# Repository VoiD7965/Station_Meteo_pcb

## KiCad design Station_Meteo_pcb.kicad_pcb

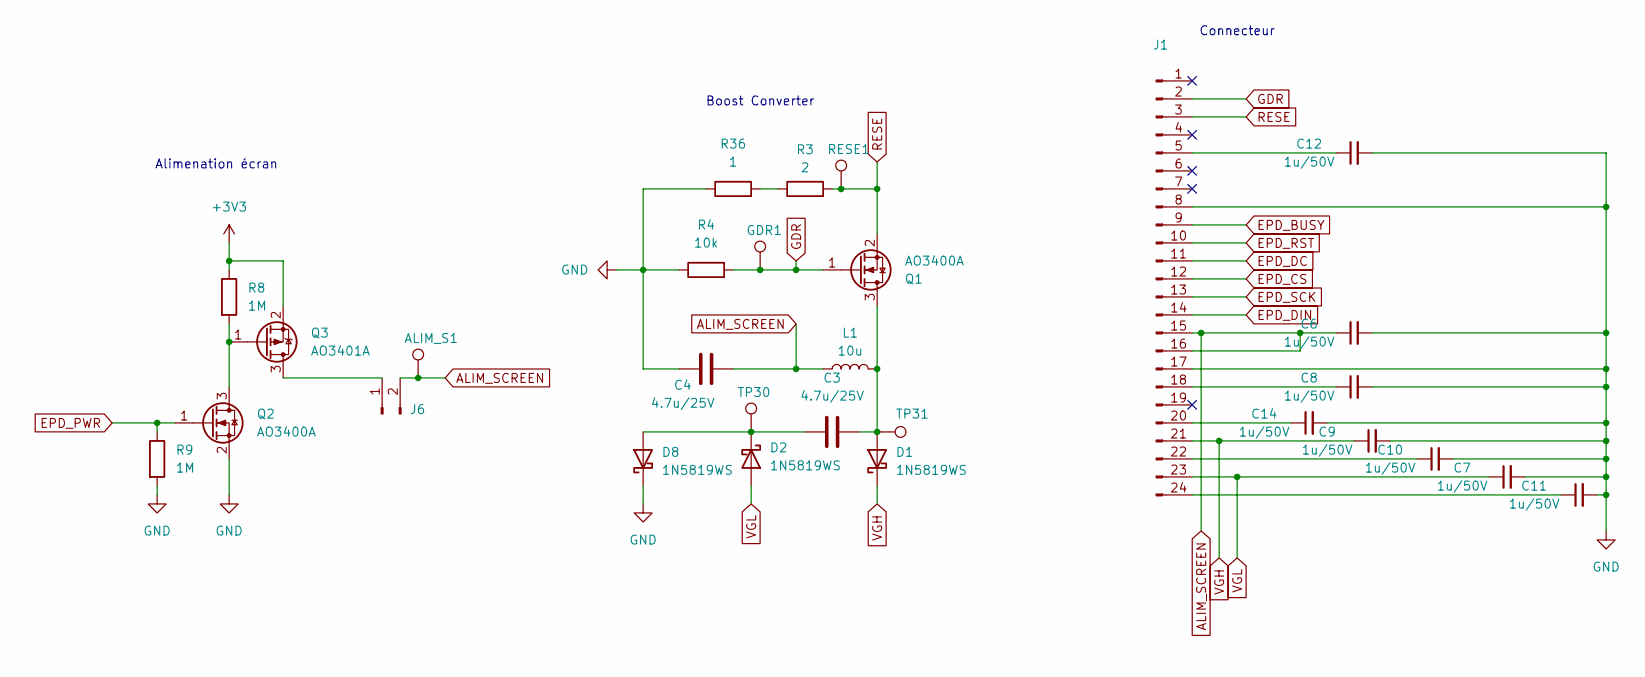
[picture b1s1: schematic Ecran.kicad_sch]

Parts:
ALIM_S1: TestPoint; TestPoint_Pad_D1.5mm
C3, C4: 4.7u/25V; C_0805_2012Metric; LCSC C1779
C6, C7, C8, C9, C10, C11, C12, C14: 1u/50V; C_0603_1608Metric; LCSC C15849
D1, D2, D8: 1N5819WS; D_SOD-323; LCSC C191023
GDR1: TestPoint; TestPoint_Pad_D1.5mm
J1: ZX-FPC-FWSX0.5PH224; Connector_1x24_epaper; LCSC C7419878
J6: DZ254S-11-02-48; PinHeader_1x02_P2.54mm_Vertical_SMD_Pin1Left; LCSC C5160785
L1: 10u; L_0805_2012Metric; LCSC C1046
Q1, Q2: AO3400A; SOT-23; LCSC C20917
Q3: AO3401A; SOT-23; LCSC C15127
R3: 2; R_0603_1608Metric; LCSC C22977
R4: 10k; R_0603_1608Metric; LCSC C25804
R8, R9: 1M; R_0603_1608Metric; LCSC C22935
R36: 1; R_0603_1608Metric; LCSC C22936
RESE1: TestPoint; TestPoint_Pad_D1.5mm
TP30, TP31: TestPoint; TestPoint_Pad_D1.5mm

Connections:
+3V3: Q3.2 (S), R8.1; also elsewhere on the board
ALIM_SCREEN: ALIM_S1.1, C4.2, C6.1, J1.15, J1.16, J6.2, L1.1
EPD_BUSY: J1.9; also elsewhere on the board
EPD_CS: J1.12; also elsewhere on the board
EPD_DC: J1.11; also elsewhere on the board
EPD_DIN: J1.14; also elsewhere on the board
EPD_PWR: Q2.1 (G), R9.1; also elsewhere on the board
EPD_RST: J1.10; also elsewhere on the board
EPD_SCK: J1.13; also elsewhere on the board
GDR: GDR1.1, J1.2, Q1.1 (G), R4.2
GND: C4.1, C6.2, C7.2, C8.2, C9.2, C10.2, C11.2, C12.2, C14.2, D8.1 (K), J1.8, J1.17, Q2.2 (S), R4.1, R9.2, R36.1; also elsewhere on the board
unnamed: C3.2, D1.2 (A), L1.2, Q1.3 (D), TP31.1
unnamed: C3.1, D2.1 (K), D8.2 (A), TP30.1
unnamed: C12.1, J1.5
unnamed: C8.1, J1.18
unnamed: C14.1, J1.20
unnamed: C10.1, J1.22
unnamed: C11.1, J1.24
unnamed: J6.1, Q3.3 (D)
unnamed: Q2.3 (D), Q3.1 (G), R8.2
unnamed: R3.1, R36.2
RESE: J1.3, Q1.2 (S), R3.2, RESE1.1
VGH: C9.1, D1.1 (K), J1.21
VGL: C7.1, D2.2 (A), J1.23

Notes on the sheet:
Alimenation écran
Boost Converter
Connecteur

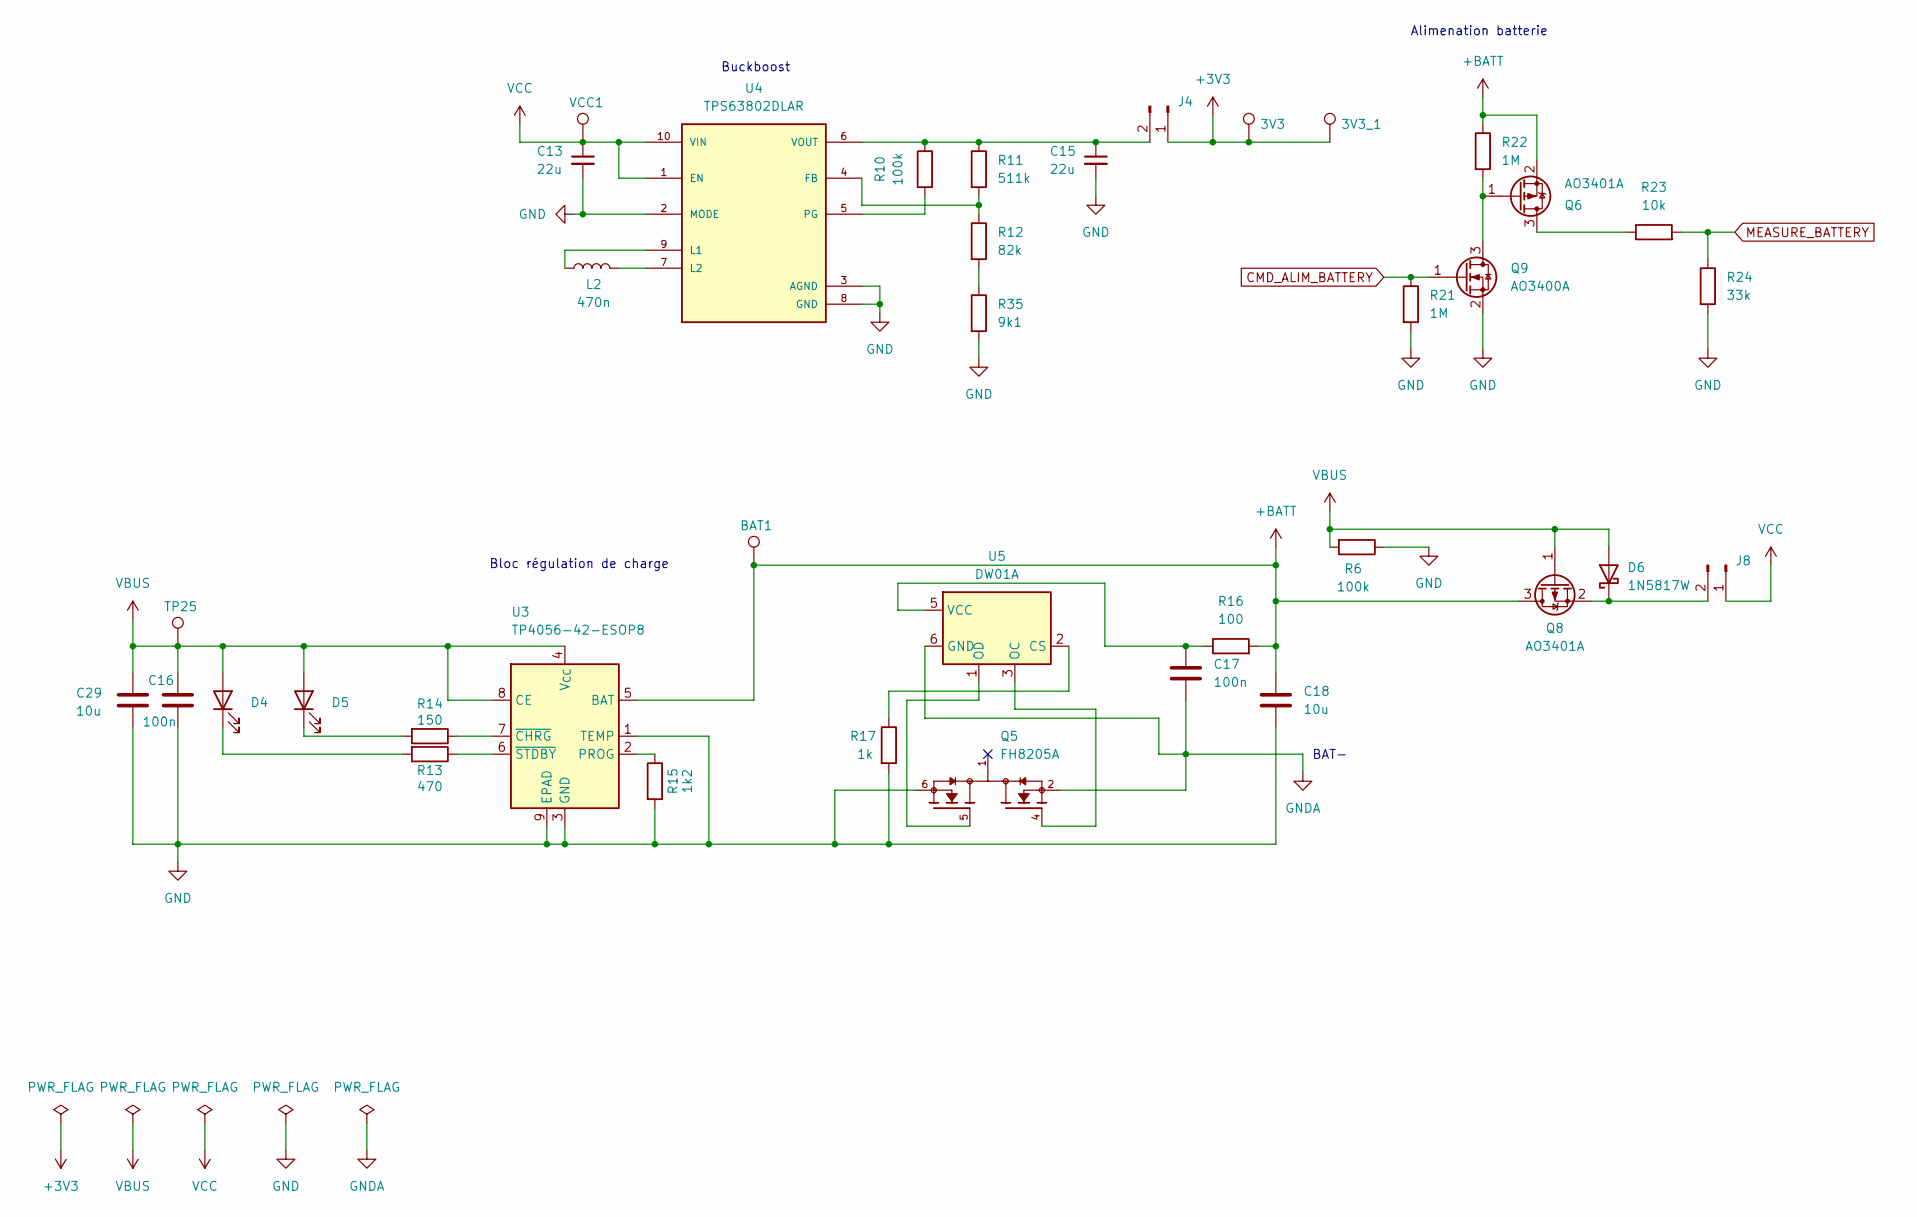
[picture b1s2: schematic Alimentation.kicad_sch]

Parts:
3V3, 3V3_1: TestPoint; TestPoint_Pad_D1.5mm
BAT1: TestPoint; TestPoint_Pad_D1.5mm
C13, C15: 22u; C_0603_1608Metric; LCSC C59461
C16, C17: 100n; C_0402_1005Metric; LCSC C1525
C18, C29: 10u; C_0603_1608Metric; LCSC C19702
D4: KT-0603W; LED_0603_1608Metric; LCSC C2290
D5: KT-0603R; LED_0603_1608Metric; LCSC C2286
D6: 1N5817W; D_SOD-123; LCSC C5185908
J4, J8: DZ254S-11-02-48; PinHeader_1x02_P2.54mm_Vertical_SMD_Pin1Left; LCSC C5160785
L2: 470n; SPM4030T-R47M-HZ; LCSC C531455
Q5: FH8205A; FS8205A; PARTREV 1.7; LCSC C2929075
Q6, Q8: AO3401A; SOT-23; LCSC C15127
Q9: AO3400A; SOT-23; LCSC C20917
R6, R10: 100k; R_0603_1608Metric; LCSC C25803
R11: 511k; R_0603_1608Metric; LCSC C23192
R12: 82k; R_0603_1608Metric; LCSC C23254
R13: 470; R_0603_1608Metric; LCSC C23179
R14: 150; R_0603_1608Metric; LCSC C22808
R15: 1k2; R_0603_1608Metric; LCSC C22765
R16: 100; R_0603_1608Metric; LCSC C22775
R17: 1k; R_0603_1608Metric; LCSC C21190
R21, R22: 1M; R_0603_1608Metric; LCSC C22935
R23: 10k; R_0603_1608Metric; LCSC C25804
R24: 33k; R_0603_1608Metric; LCSC C4216
R35: 9k1; R_0603_1608Metric; LCSC C23260
TP25: TestPoint; TestPoint_Pad_D1.5mm
U3: TP4056-42-ESOP8; SOIC-8-1EP_3.9x4.9mm_P1.27mm_EP2.41x3.3mm_ThermalVias; LCSC C16581
U4: TPS63802DLAR; VREG_TPS63802DLAR; PARTREV B; LCSC C2845237
U5: DW01A; SOT-23-6; LCSC C42380662
VCC1: TestPoint; TestPoint_Pad_D1.5mm

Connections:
+3V3: 3V3.1, 3V3_1.1, J4.1; also elsewhere on the board
+BATT: BAT1.1, C18.1, Q6.2 (S), Q8.3 (D), R16.2, R22.1, U3.5 (BAT); also elsewhere on the board
CMD_ALIM_BATTERY: Q9.1 (G), R21.1; also elsewhere on the board
GND: C13.2, C15.2, C16.2, C18.2, C29.1, Q5.6, Q5.7, Q9.2 (S), R6.1, R15.2, R17.2, R21.2, R24.2, R35.2, U3.1 (TEMP), U3.3 (GND), U3.9 (EPAD), U4.2 (MODE), U4.3 (AGND), U4.8 (GND); also elsewhere on the board
GNDA: C17.2, Q5.2, Q5.3, U5.6 (GND); also elsewhere on the board
MEASURE_BATTERY: R23.2, R24.1; also elsewhere on the board
unnamed: D4.1 (K), R13.2
unnamed: D5.1 (K), R14.2
unnamed: D6.1 (K), J8.2, Q8.2 (S)
unnamed: C15.1, J4.2, R10.1, R11.1, U4.6 (VOUT)
unnamed: Q6.3 (D), R23.1
unnamed: Q6.1 (G), Q9.3 (D), R22.2
unnamed: R12.2, R35.1
unnamed: R15.1, U3.2 (PROG)
unnamed: R14.1, U3.7 (~CHRG)
unnamed: R13.1, U3.6 (~STDBY)
unnamed: R11.2, R12.1, U4.4 (FB)
unnamed: L2.1, U4.9 (L1)
unnamed: L2.2, U4.7 (L2)
unnamed: R10.2, U4.5 (PG)
unnamed: R17.1, U5.2 (CS)
unnamed: Q5.4, U5.3 (OC)
unnamed: Q5.5, U5.1 (OD)
unnamed: C17.1, R16.1, U5.5 (VCC)
VBUS: C16.1, C29.2, D4.2 (A), D5.2 (A), D6.2 (A), Q8.1 (G), R6.2, TP25.1, U3.4 (V_{CC}), U3.8 (CE); also elsewhere on the board
VCC: C13.1, J8.1, U4.1 (EN), U4.10 (VIN), VCC1.1

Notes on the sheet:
BAT-
Alimenation batterie
Buckboost
Bloc régulation de charge

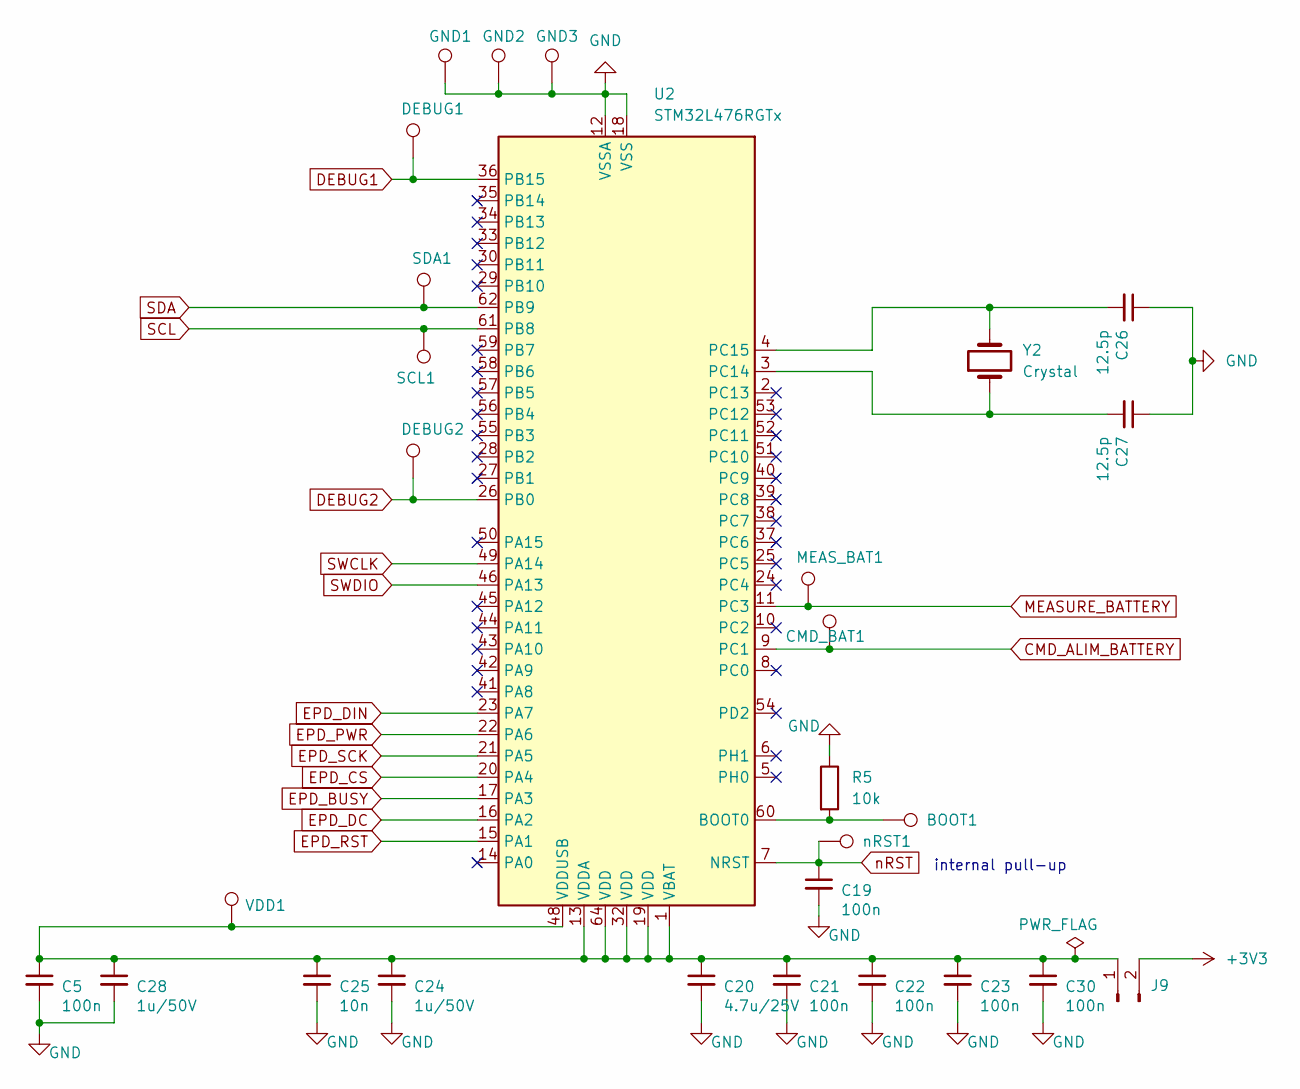
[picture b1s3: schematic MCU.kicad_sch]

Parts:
BOOT1: TestPoint; TestPoint_Pad_D1.5mm
C5, C19, C21, C22, C23, C30: 100n; C_0402_1005Metric; LCSC C1525
C20: 4.7u/25V; C_0805_2012Metric; LCSC C1779
C24, C28: 1u/50V; C_0603_1608Metric; LCSC C15849
C25: 10n; C_0603_1608Metric; LCSC C57112
C26, C27: 12.5p; C_0402_1005Metric; LCSC C1547
CMD_BAT1: TestPoint; TestPoint_Pad_D1.5mm
DEBUG1, DEBUG2: TestPoint; TestPoint_Pad_D1.5mm
GND1, GND2, GND3: TestPoint; TestPoint_Pad_D1.5mm
J9: DZ254S-11-02-48; PinHeader_1x02_P2.54mm_Vertical_SMD_Pin1Left; LCSC C5160785
MEAS_BAT1: TestPoint; TestPoint_Pad_D1.5mm
R5: 10k; R_0603_1608Metric; LCSC C25804
SCL1: TestPoint; TestPoint_Pad_D1.5mm
SDA1: TestPoint; TestPoint_Pad_D1.5mm
U2: STM32L476RGTx; LQFP-64_10x10mm_P0.5mm; LCSC C74797
VDD1: TestPoint; TestPoint_Pad_D1.5mm
Y2: Crystal; Crystal_SMD_3215-2Pin_3.2x1.5mm; LCSC C2450907
nRST1: TestPoint; TestPoint_Pad_D1.5mm

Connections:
+3V3: J9.2; also elsewhere on the board
CMD_ALIM_BATTERY: CMD_BAT1.1, U2.9 (PC1); also elsewhere on the board
DEBUG1: DEBUG1.1, U2.36 (PB15)
DEBUG2: DEBUG2.1, U2.26 (PB0)
EPD_BUSY: U2.17 (PA3); also elsewhere on the board
EPD_CS: U2.20 (PA4); also elsewhere on the board
EPD_DC: U2.16 (PA2); also elsewhere on the board
EPD_DIN: U2.23 (PA7); also elsewhere on the board
EPD_PWR: U2.22 (PA6); also elsewhere on the board
EPD_RST: U2.15 (PA1); also elsewhere on the board
EPD_SCK: U2.21 (PA5); also elsewhere on the board
GND: C5.2, C19.2, C20.2, C21.2, C22.2, C23.2, C24.2, C25.2, C26.1, C27.1, C28.2, C30.2, GND1.1, GND2.1, GND3.1, R5.1, U2.12 (VSSA), U2.18 (VSS), U2.31 (VSS), U2.47 (VSS), U2.63 (VSS); also elsewhere on the board
MEASURE_BATTERY: MEAS_BAT1.1, U2.11 (PC3); also elsewhere on the board
unnamed: C5.1, C20.1, C21.1, C22.1, C23.1, C24.1, C25.1, C28.1, C30.1, J9.1, U2.1 (VBAT), U2.13 (VDDA), U2.19 (VDD), U2.32 (VDD), U2.48 (VDDUSB), U2.64 (VDD), VDD1.1
unnamed: BOOT1.1, R5.2, U2.60 (BOOT0)
unnamed: C27.2, U2.3 (PC14), Y2.1
unnamed: C26.2, U2.4 (PC15), Y2.2
SCL: SCL1.1, U2.61 (PB8); also elsewhere on the board
SDA: SDA1.1, U2.62 (PB9); also elsewhere on the board
SWCLK: U2.49 (PA14); also elsewhere on the board
SWDIO: U2.46 (PA13); also elsewhere on the board
nRST: C19.1, U2.7 (NRST), nRST1.1; also elsewhere on the board

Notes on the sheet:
internal pull-up

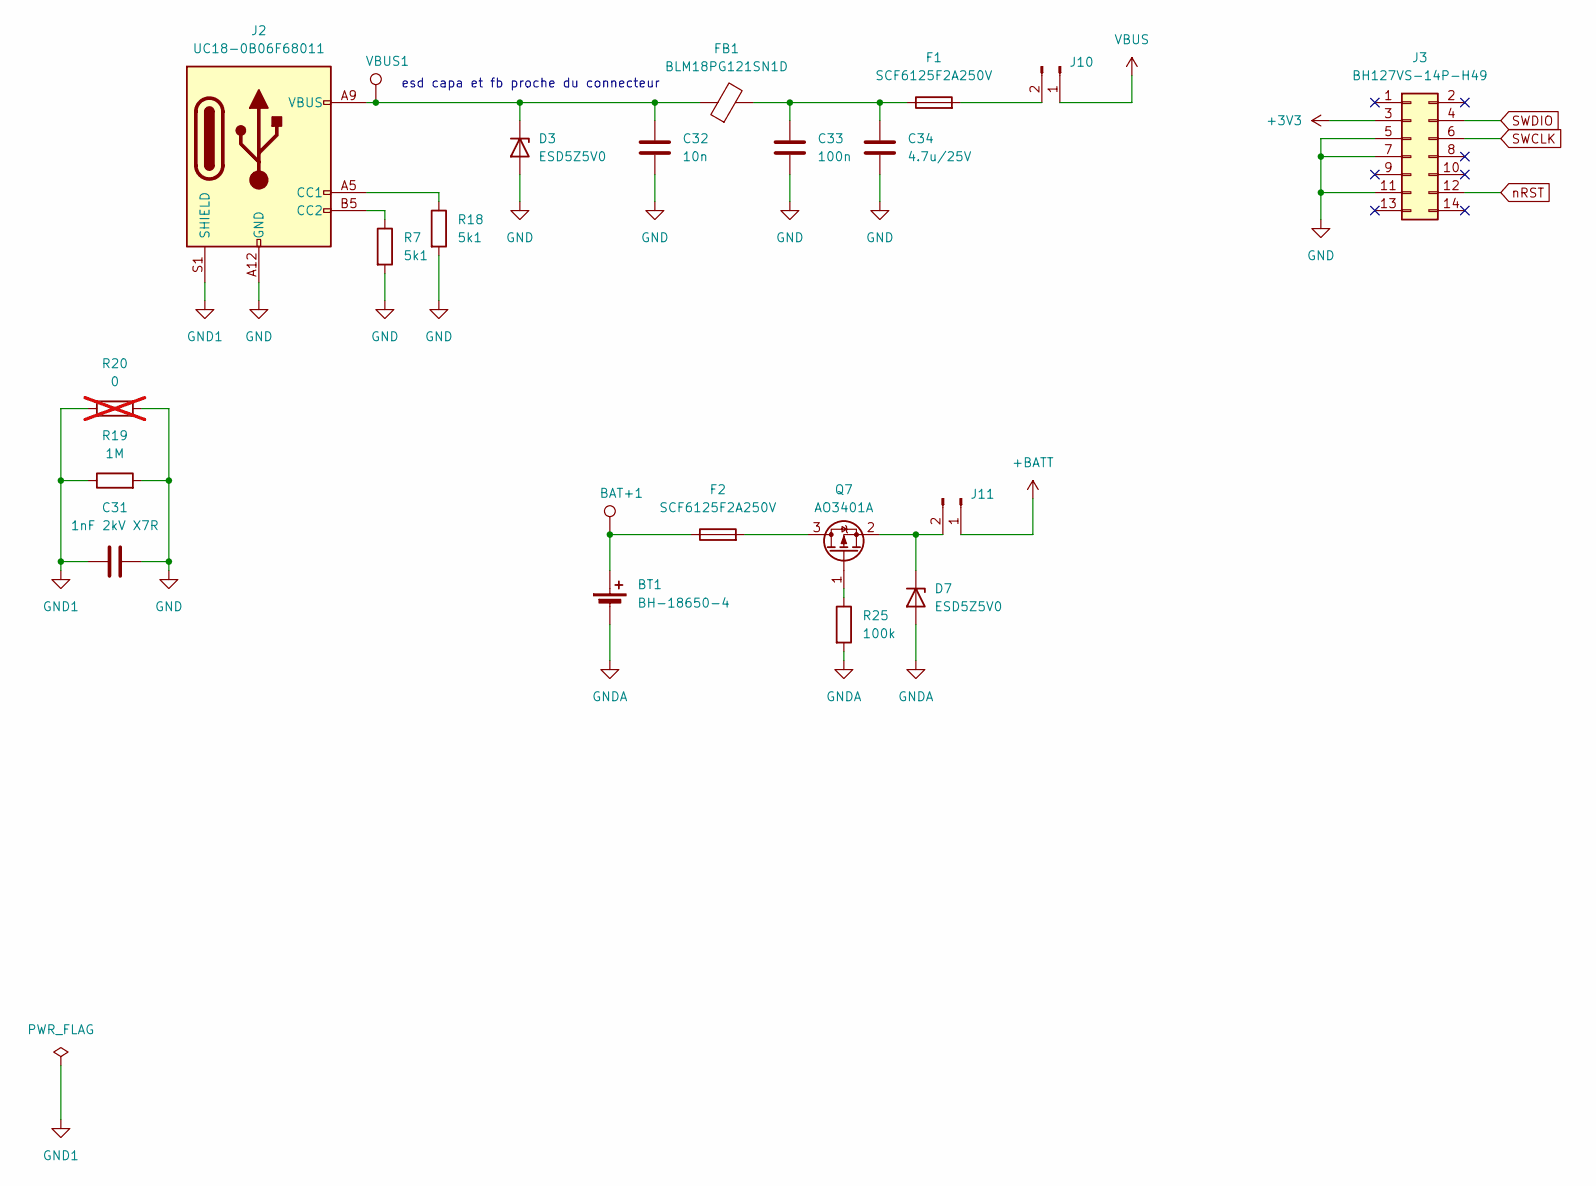
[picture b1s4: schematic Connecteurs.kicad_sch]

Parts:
BAT+1: TestPoint; TestPoint_Pad_D1.5mm
BT1: BH-18650-4; LCSC C7525438
C31: 1nF 2kV X7R; C_1206_3216Metric; LCSC C9196
C32: 10n; C_0603_1608Metric; LCSC C57112
C33: 100n; C_0402_1005Metric; LCSC C1525
C34: 4.7u/25V; C_0805_2012Metric; LCSC C1779
D3, D7: ESD5Z5V0; D_SOD-523; LCSC C21714169
F1, F2: SCF6125F2A250V; LCSC C19712554
FB1: BLM18PG121SN1D; L_0603_1608Metric; LCSC C14709
J2: UC18-0B06F68011; LCSC C36936555
J3: BH127VS-14P-H49; Connector_STLINKV3_Minie_14P; LCSC C42462827
J10, J11: DZ254S-11-02-48; PinHeader_1x02_P2.54mm_Vertical_SMD_Pin1Left; LCSC C5160785
Q7: AO3401A; SOT-23; LCSC C15127
R7, R18: 5k1; R_0603_1608Metric; LCSC C23186
R19: 1M; R_0603_1608Metric; LCSC C22935
R20: 0; R_0603_1608Metric; not fitted
R25: 100k; R_0603_1608Metric; LCSC C25803
VBUS1: TestPoint; TestPoint_Pad_D1.5mm

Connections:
+3V3: J3.3; also elsewhere on the board
+BATT: J11.1; also elsewhere on the board
GND: C31.2, C32.2, C33.2, C34.2, D3.2 (A), J2.A12 (GND), J2.B12 (GND), J3.5, J3.7, J3.11, R7.2, R18.2, R19.2, R20.2; also elsewhere on the board
GND1: C31.1, J2.S1 (SHIELD), R19.1, R20.1
GNDA: BT1.2 (-), D7.2 (A), R25.2; also elsewhere on the board
unnamed: BAT+1.1, BT1.1 (+), F2.1
unnamed: C33.1, C34.1, F1.1, FB1.2
unnamed: C32.1, D3.1 (K), FB1.1, J2.A9 (VBUS), J2.B9 (VBUS), VBUS1.1
unnamed: D7.1 (K), J11.2, Q7.2 (S)
unnamed: J2.A5 (CC1), R18.1
unnamed: J2.B5 (CC2), R7.1
unnamed: F1.2, J10.2
unnamed: F2.2, Q7.3 (D)
unnamed: Q7.1 (G), R25.1
SWCLK: J3.6; also elsewhere on the board
SWDIO: J3.4; also elsewhere on the board
VBUS: J10.1; also elsewhere on the board
nRST: J3.12; also elsewhere on the board

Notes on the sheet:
esd capa et fb proche du connecteur

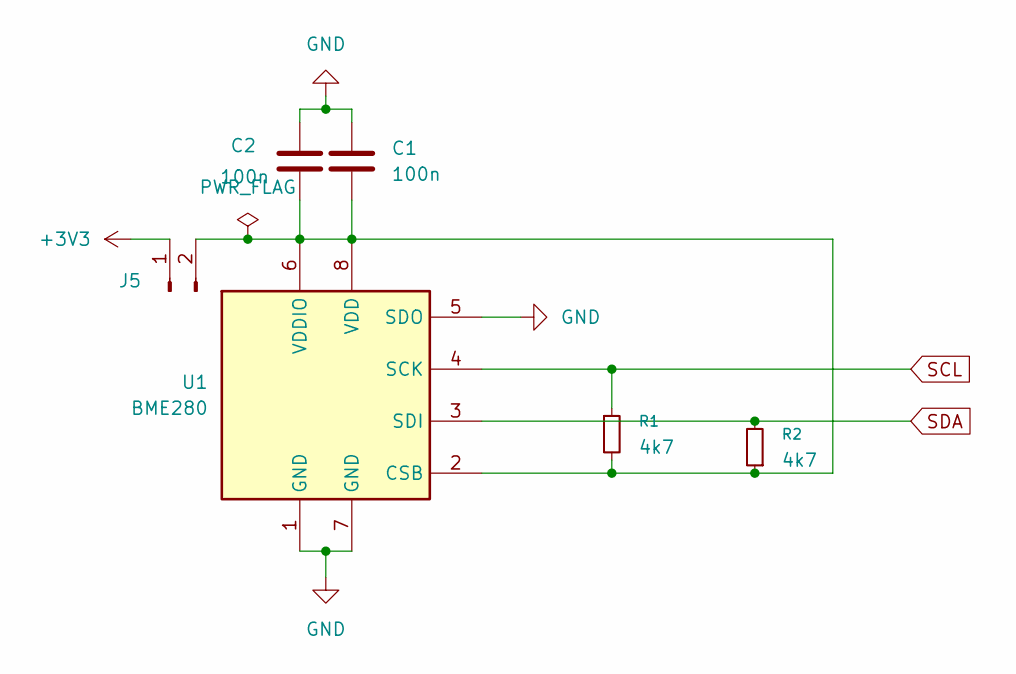
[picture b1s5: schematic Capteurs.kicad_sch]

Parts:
C1, C2: 100n; C_0402_1005Metric; LCSC C1525
J5: DZ254S-11-02-48; PinHeader_1x02_P2.54mm_Vertical_SMD_Pin1Left; LCSC C5160785
R1, R2: 4k7; R_0603_1608Metric; LCSC C23162
U1: BME280; Bosch_LGA-8_2.5x2.5mm_P0.65mm_ClockwisePinNumbering; LCSC C92489

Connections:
+3V3: J5.1; also elsewhere on the board
GND: C1.2, C2.1, U1.1 (GND), U1.5 (SDO), U1.7 (GND); also elsewhere on the board
unnamed: C1.1, C2.2, J5.2, R1.2, R2.1, U1.2 (CSB), U1.6 (VDDIO), U1.8 (VDD)
SCL: R1.1, U1.4 (SCK); also elsewhere on the board
SDA: R2.2, U1.3 (SDI); also elsewhere on the board

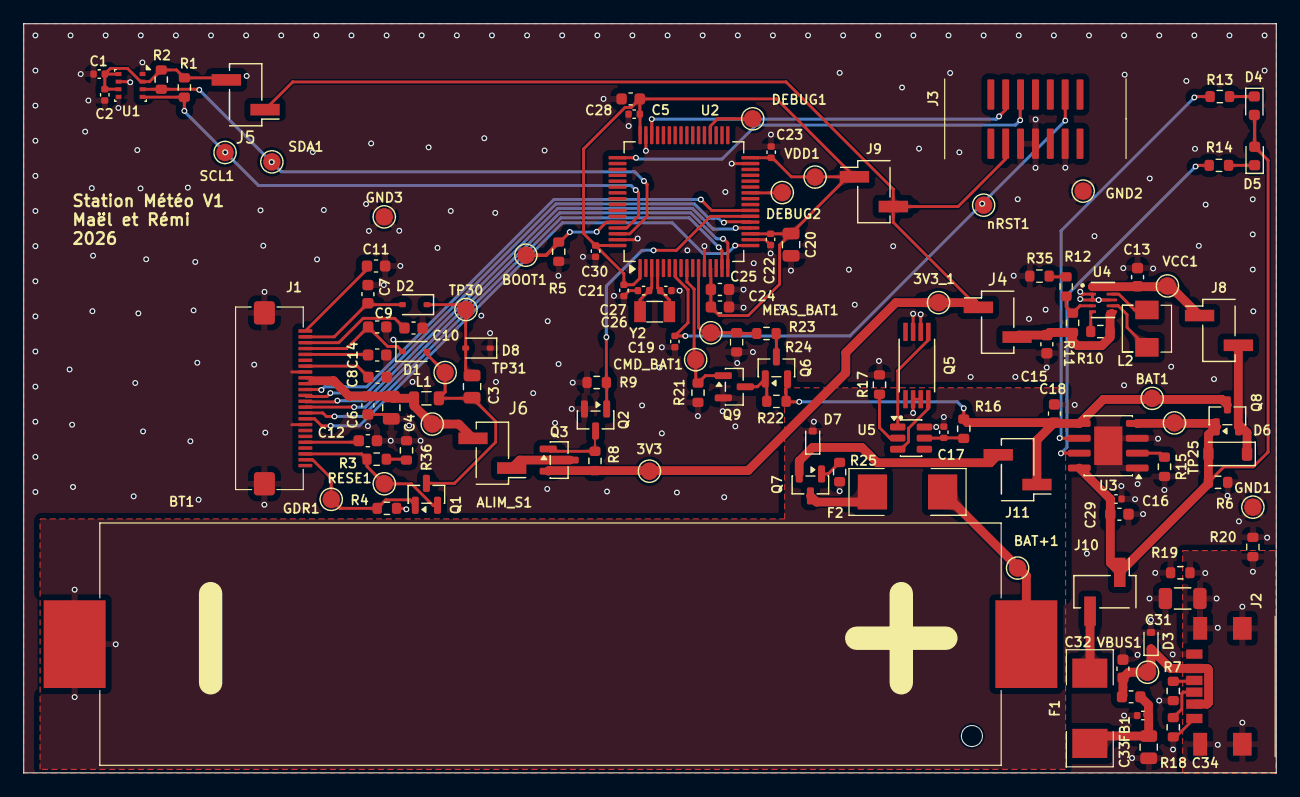
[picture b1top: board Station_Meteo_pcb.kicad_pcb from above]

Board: 2 copper layers, 107.0 x 64.0 mm, 123 parts (0 on the bottom side), 70 nets.

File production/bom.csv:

Designator,Footprint,Quantity,Value,LCSC Part #
BT1,BH-18650-4,1,BH-18650-4,C49118399
"C1, C16, C17, C19, C2, C21, C22, C23, C30, C33, C5",0402,11,100n,C1525
"C10, C11, C12, C14, C24, C28, C6, C7, C8, C9",0603,10,1u/50V,C15849
"C13, C15",0603,2,22u,C59461
"C18, C29",0603,2,10u,C19702
"C20, C3, C34, C4",0805,4,4.7u/25V,C1779
"C25, C32",0603,2,10n,C57112
"C26, C27",0402,2,12.5p,C1547
C31,1206,1,1nF 2kV X7R,C9196
"D1, D2, D8",D_SOD-323,3,1N5819WS,C191023
"D3, D7",D_SOD-523,2,ESD5Z5V0,C21714169
D4,0603,1,KT-0603W,C2290
D5,0603,1,KT-0603R,C2286
D6,D_SOD-123,1,1N5817W,C5185908
"F1, F2",SCF6125F2A250V,2,SCF6125F2A250V,C19712554
FB1,0603,1,BLM18PG121SN1D,C14709
J1,Connector_1x24_epaper,1,ZX-FPC-FWSX0.5PH224,C7419878
"J10, J11, J4, J5, J6, J8, J9",PinHeader_1x02_P2.54mm_Vertical_SMD_Pin1Left,7,DZ254S-11-02-48,C5160785
J2,UC18-0B06F68011,1,UC18-0B06F68011,C36936555
J3,Connector_STLINKV3_Minie_14P,1,BH127VS-14P-H49,C42462827
L1,0805,1,10u,C1046
L2,SPM4030T-R47M-HZ,1,470n,C531455
"Q1, Q2, Q9",SOT-23,3,AO3400A,C20917
"Q3, Q6, Q7, Q8",SOT-23,4,AO3401A,C15127
Q5,FS8205A,1,FS8205A,C2830320
"R1, R2",0603,2,4k7,C23162
"R10, R25, R6",0603,3,100k,C25803
R11,0603,1,511k,C23192
R12,0603,1,82k,C23254
R13,0603,1,470,C23179
R14,0603,1,150,C22808
R15,0603,1,1k2,C22765
R16,0603,1,100,C22775
R17,0603,1,1k,C21190
"R18, R7",0603,2,5k1,C23186
"R19, R21, R22, R8, R9",0603,5,1M,C22935
"R23, R4, R5",0603,3,10k,C25804
R24,0603,1,33k,C4216
R3,0603,1,2,C22977
R35,0603,1,9k1,C23260
R36,0603,1,1,C22936
U1,Bosch_LGA-8_2.5x2.5mm_P0.65mm_ClockwisePinNumbering,1,BME280,C92489
U2,LQFP-64_10x10mm_P0.5mm,1,STM32L476RGTx,C74797
U3,SOIC-8-1EP_3.9x4.9mm_P1.27mm_EP2.41x3.3mm_ThermalVias,1,TP4056-42-ESOP8,C16581
U4,VREG_TPS63802DLAR,1,TPS63802DLAR,C2845237
U5,SOT-23-6,1,DW01A,C42380662
Y2,Crystal_SMD_3215-2Pin_3.2x1.5mm,1,Crystal,C2450907

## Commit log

2026-03-22 first push
2026-03-22 test
2026-03-22 Schematique Capteurs
    Mise en forme des pages pour les différents schémas kicad
    Pages capteurs mais à vérifier
2026-03-23 Test ajout de composant depuis l'internet
2026-03-23 Correction capteur + ajout composant
    Il fallait changer le nom dans le gestionnaire de footprint
    Correction de la connectique du capteur, mais à vérifier quand même
2026-03-23 Partie écran
2026-03-23 Début de la partie alimentation
2026-03-24 Ajout total de la partie alimentation
    Ajout de composant depuis un site internet ->OK
    Fin de la partie écran et alimentation : ajout de tous les composants
2026-03-25 Début Debug + MAJ MCU
2026-03-31 Dernieres pour review
2026-04-02 revue schema
2026-04-04 premieres modif depuis la review
2026-04-05 schema v1
2026-04-05 shema v1
2026-04-10 Connecteurs + sourcing
2026-04-15 placement
2026-04-23 push routage
2026-04-24 Suite routage (vers pile)
2026-04-24 V1 Placement + Routage
2026-04-26 revue
2026-04-26 TEST POINT
2026-04-27 Placement + routage V2
2026-04-27 comit
2026-04-27 Correction des erreurs (DRC)
2026-04-27 Suite DRC
2026-04-27 pusg
2026-04-28 Placement + routage V3
2026-05-03 push
2026-05-04 Commande
2026-05-05 modif pour commande
2026-05-05 last push
2026-05-05 last p
2026-05-17 Commande PCB finale
